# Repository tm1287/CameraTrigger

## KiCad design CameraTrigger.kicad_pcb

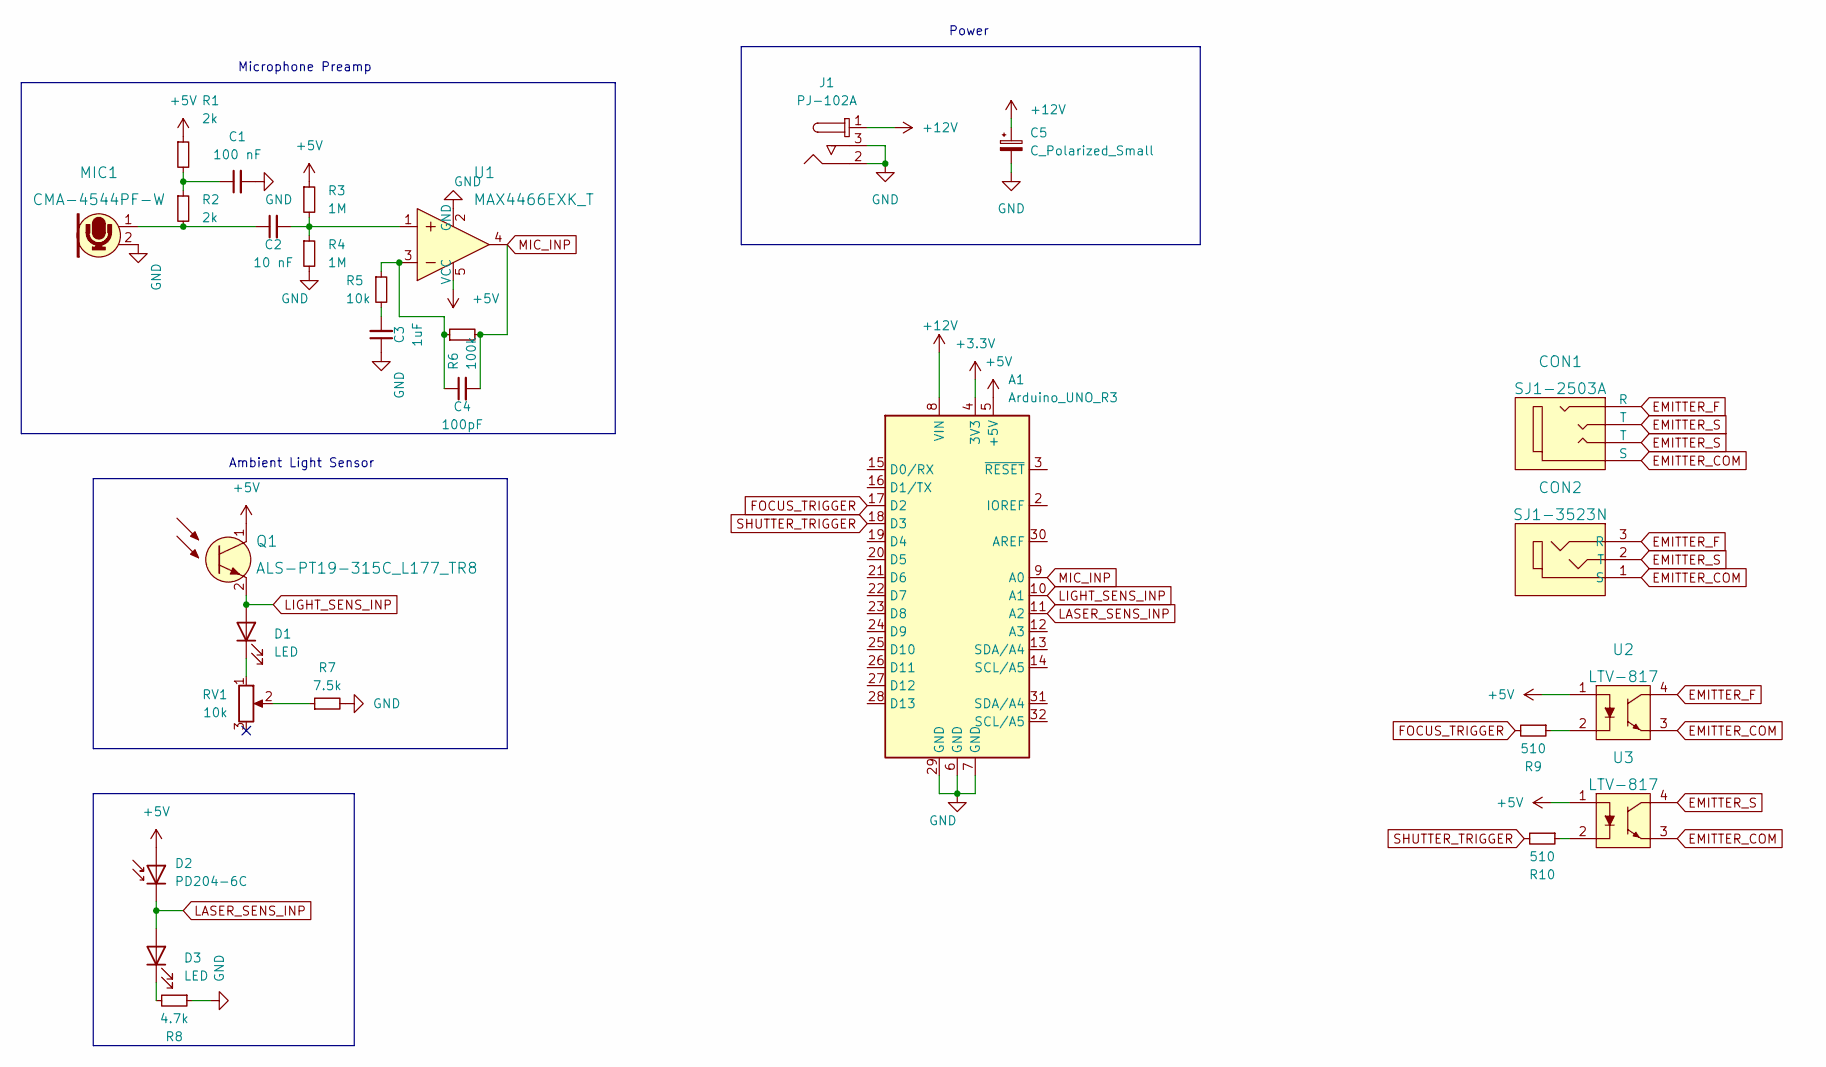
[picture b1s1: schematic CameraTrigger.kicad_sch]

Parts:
A1: Arduino_UNO_R3
C1: 100 nF; C_0805_2012Metric; LCSC C28233
C2: 10 nF; C_0805_2012Metric; LCSC C1710
C3: 1uF; C_0805_2012Metric; LCSC C28323
C4: 100pF; C_0805_2012Metric; LCSC C1790
C5: C_Polarized_Small; CP_EIA-3528-15_AVX-H
CON1: SJ1-2503A; Headphone_Jack_2.5mm_SJ1-2503A; MPN SJ1-2503A; Digi-Key_PN CP1-2503A-ND
CON2: SJ1-3523N; Headphone_Jack_3.5mm_SJ1-3523N; MPN SJ1-3523N; Digi-Key_PN CP1-3523N-ND
D1, D3: LED; LED_D3.0mm
D2: PD204-6C; LED_D3.0mm
J1: PJ-102A; Barrel_Jack_5.5mmODx2.1mmID_PJ-102A; MPN PJ-102A; Digi-Key_PN CP-102A-ND
MIC1: CMA-4544PF-W; Mic_CMA-4544PF-W; MPN CMA-4544PF-W; Digi-Key_PN 102-1721-ND
Q1: ALS-PT19-315C_L177_TR8; LED_2-SMD_No_Lead_1.7x0.8mm; MPN ALS-PT19-315C/L177/TR8; Digi-Key_PN 1080-1244-1-ND
R1, R2: 2k; R_0805_2012Metric; LCSC C17604
R3, R4: 1M; R_0805_2012Metric; LCSC C17514
R5: 10k; R_0805_2012Metric; LCSC C17414
R6: 100k; R_0805_2012Metric; LCSC C149504
R7: 7.5k; R_0805_2012Metric; LCSC C17807
R8: 4.7k; R_0805_2012Metric; LCSC C17673
R9, R10: 510; R_0805_2012Metric; LCSC C17734
RV1: 10k; Potentiometer_Piher_PT-10-V10_Vertical
U1: MAX4466EXK_T; SOT-353; MPN MAX4466EXK+T; Digi-Key_PN MAX4466EXK+CT-ND
U2, U3: LTV-817; DIP-4_W7.62mm; MPN LTV-817; Digi-Key_PN 160-1366-5-ND

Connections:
+3V3: A1.4 (3V3)
+5V: A1.5 (+5V), D2.2 (A), Q1.1 (C), R1.1, R3.1, U1.5 (VCC), U2.1, U3.1
+12V: A1.8 (VIN), C5.1, J1.1
EMITTER_COM: CON1.1 (S), CON2.1 (S), U2.3, U3.3
EMITTER_F: CON1.4 (R), CON2.3 (R), U2.4
EMITTER_S: CON1.2 (T), CON1.3 (T), CON2.2 (T), U3.4
FOCUS_TRIGGER: A1.17 (D2), R9.2
GND: A1.6 (GND), A1.7 (GND), A1.29 (GND), C1.2, C3.1, C5.2, J1.2, J1.3, MIC1.2, R4.2, R7.2, R8.1, U1.2 (GND)
LASER_SENS_INP: A1.11 (A2), D2.1 (K), D3.2 (A)
LIGHT_SENS_INP: A1.10 (A1), D1.2 (A), Q1.2 (E)
MIC_INP: A1.9 (A0), C4.2, R6.2, U1.4
unnamed: C1.1, R1.2, R2.1
unnamed: C2.1, MIC1.1, R2.2
unnamed: C2.2, R3.2, R4.1, U1.1
unnamed: C3.2, R5.2
unnamed: C4.1, R5.1, R6.1, U1.3
unnamed: D1.1 (K), RV1.1
unnamed: R7.1, RV1.2
unnamed: D3.1 (K), R8.2
unnamed: R9.1, U2.2
unnamed: R10.1, U3.2
SHUTTER_TRIGGER: A1.18 (D3), R10.2

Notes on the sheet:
Ambient Light Sensor
Microphone Preamp
Power

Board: 2 copper layers, 28 parts (0 on the bottom side), 21 nets, no tracks yet.

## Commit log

2022-06-20 Add microphone pre-amp circuit
2022-07-01 Add final sensors and triggering mechanisms
